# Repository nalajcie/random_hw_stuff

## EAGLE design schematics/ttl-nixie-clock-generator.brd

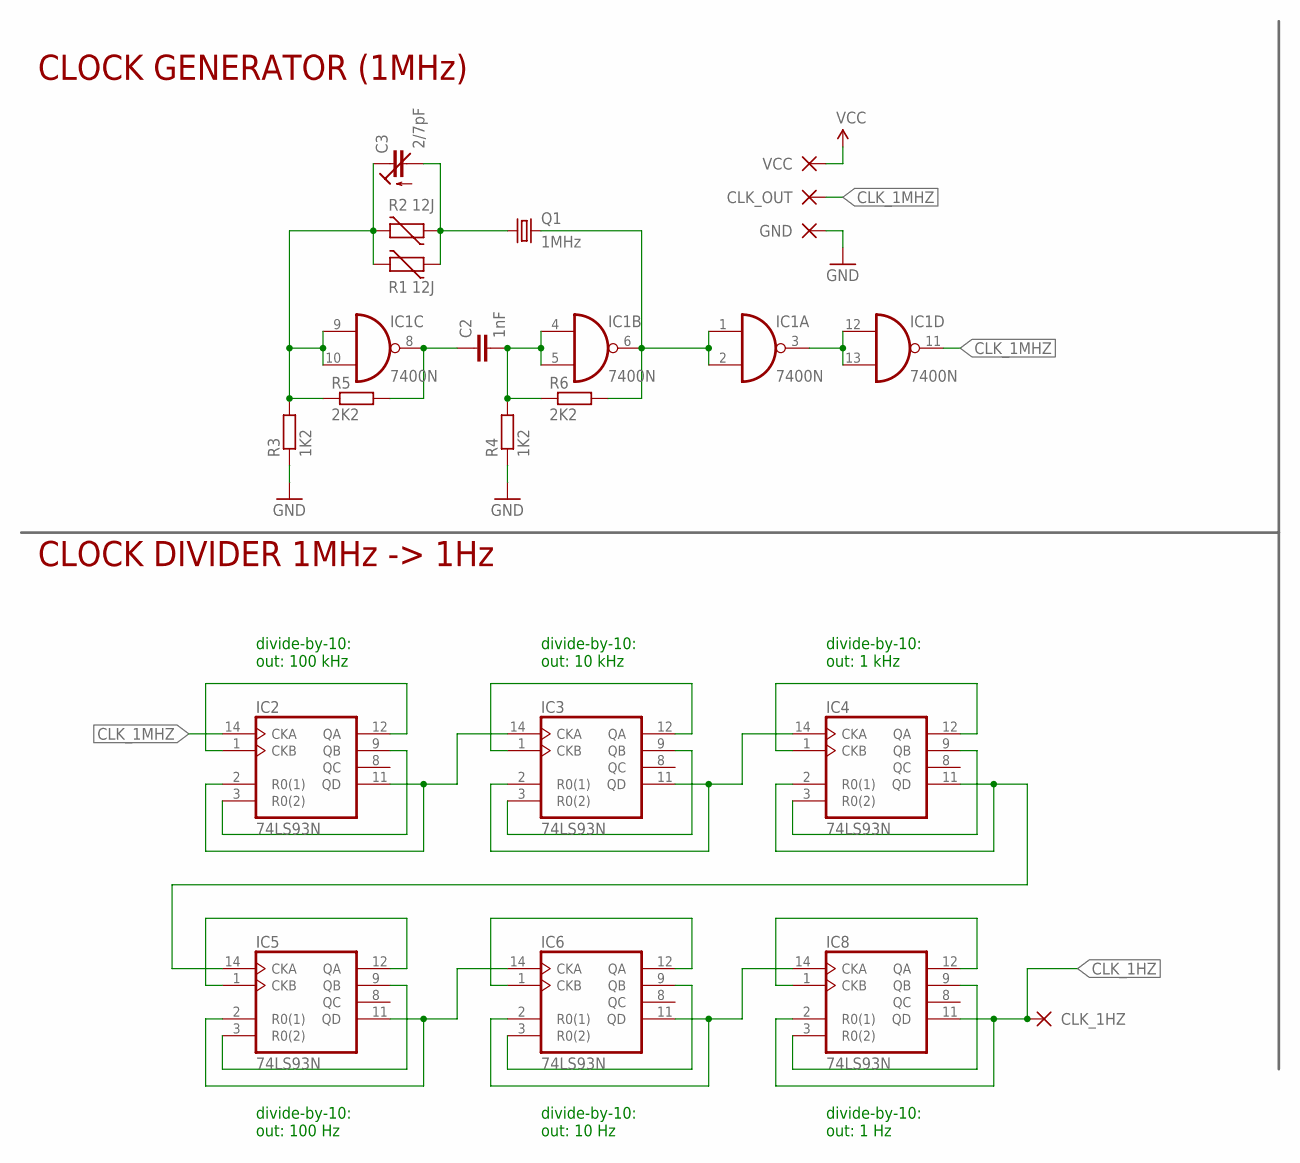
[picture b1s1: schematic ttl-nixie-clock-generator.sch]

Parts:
C2: 1nF; C15B5
C3: 2/7pF; CTRIM808-BC7.5
CLK_1HZ: VCC; 2,15/1,0
CLK_OUT: CLK_OUT; 2,15/1,0
GND: GND; 2,15/1,0
IC1: 7400N; DIL14
IC2, IC3, IC4, IC5, IC6, IC8: 74LS93N; DIL14
Q1: 1MHz; HC33U-V
R1, R2: 12J; R-7,5
R3, R4: 1K2; 0207/12
R5, R6: 2K2; 0207/12
VCC: VCC; 2,15/1,0

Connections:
CLK_1HZ: CLK_1HZ.1, IC8.2 (R0(1)), IC8.11 (QD)
CLK_1MHZ: CLK_OUT.1, IC1.11 (O), IC2.14 (CKA)
GND: GND.1, IC1.7 (GND), IC2.10 (GND), IC3.10 (GND), IC4.10 (GND), IC5.10 (GND), IC6.10 (GND), IC8.10 (GND), R3.1, R4.1
unnamed: C3.2 (A), Q1.1, R1.1, R2.1
unnamed: C3.1 (E), IC1.9 (I0), IC1.10 (I1), R1.2, R2.2, R3.2, R5.1
unnamed: IC1.3 (O), IC1.12 (I0), IC1.13 (I1)
unnamed: C2.1, IC1.8 (O), R5.2
unnamed: C2.2, IC1.4 (I0), IC1.5 (I1), R4.2, R6.1
unnamed: IC1.1 (I0), IC1.2 (I1), IC1.6 (O), Q1.2, R6.2
unnamed: IC5.1 (CKB), IC5.12 (QA)
unnamed: IC5.3 (R0(2)), IC5.9 (QB)
unnamed: IC5.2 (R0(1)), IC5.11 (QD), IC6.14 (CKA)
unnamed: IC6.1 (CKB), IC6.12 (QA)
unnamed: IC6.3 (R0(2)), IC6.9 (QB)
unnamed: IC6.2 (R0(1)), IC6.11 (QD), IC8.14 (CKA)
unnamed: IC8.1 (CKB), IC8.12 (QA)
unnamed: IC8.3 (R0(2)), IC8.9 (QB)
unnamed: IC2.1 (CKB), IC2.12 (QA)
unnamed: IC2.2 (R0(1)), IC2.11 (QD), IC3.14 (CKA)
unnamed: IC2.3 (R0(2)), IC2.9 (QB)
unnamed: IC3.3 (R0(2)), IC3.9 (QB)
unnamed: IC3.2 (R0(1)), IC3.11 (QD), IC4.14 (CKA)
unnamed: IC3.1 (CKB), IC3.12 (QA)
unnamed: IC4.1 (CKB), IC4.12 (QA)
unnamed: IC4.3 (R0(2)), IC4.9 (QB)
unnamed: IC4.2 (R0(1)), IC4.11 (QD), IC5.14 (CKA)
VCC: IC1.14 (VCC), IC2.5 (VCC), IC3.5 (VCC), IC4.5 (VCC), IC5.5 (VCC), IC6.5 (VCC), IC8.5 (VCC), VCC.1

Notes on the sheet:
divide-by-10: out: 100 kHz
divide-by-10: out: 10 kHz
divide-by-10: out: 1 kHz
divide-by-10: out: 100 Hz
divide-by-10: out: 10 Hz
divide-by-10: out: 1 Hz
CLOCK DIVIDER 1MHz -> 1Hz
CLOCK GENERATOR (1MHz)

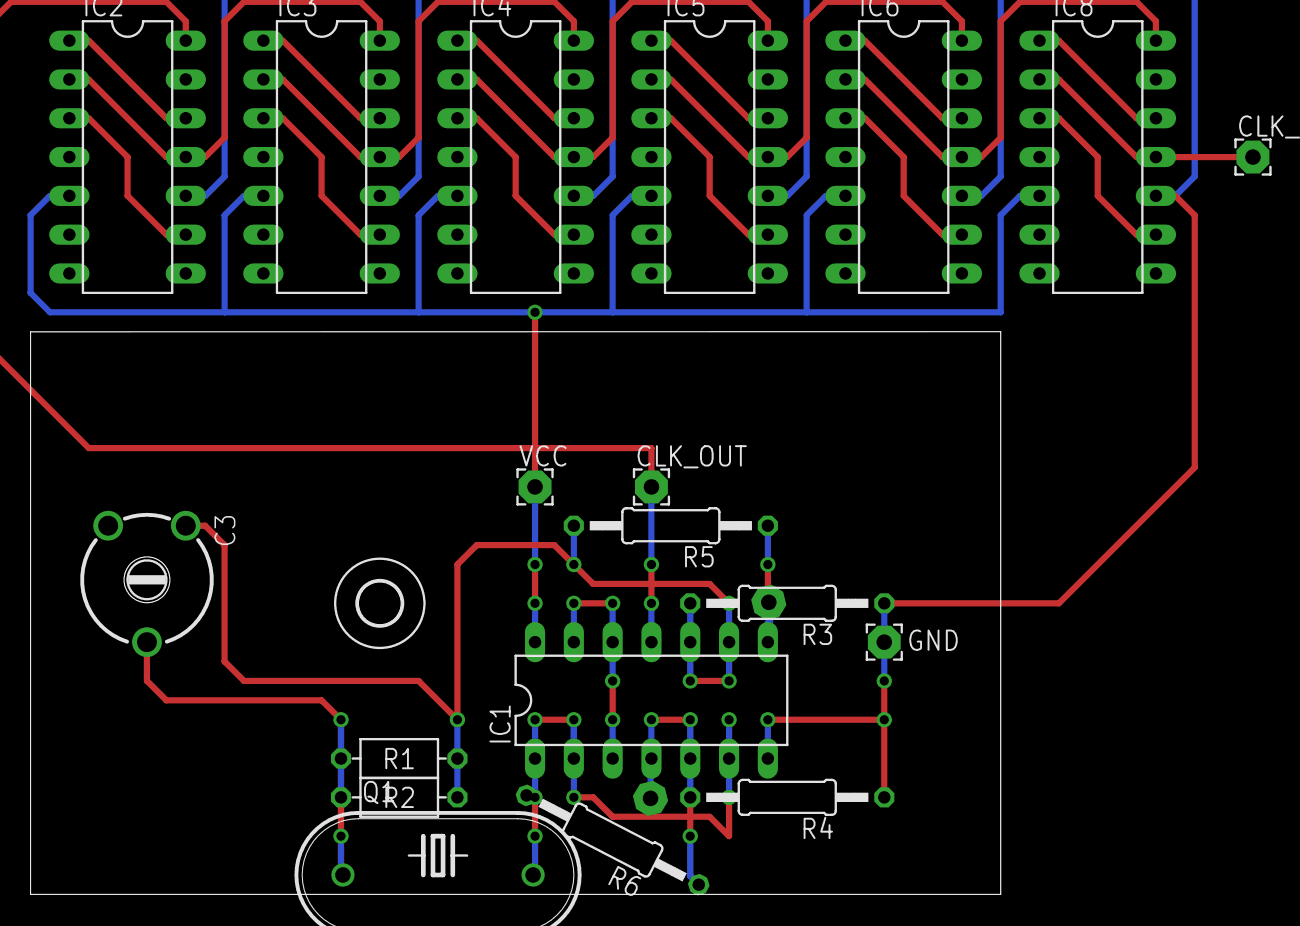
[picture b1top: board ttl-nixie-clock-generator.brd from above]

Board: 2 copper layers, 63.5 x 36.8 mm, 21 parts (1 on the bottom side), 27 nets.

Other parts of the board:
U$1: 2,8

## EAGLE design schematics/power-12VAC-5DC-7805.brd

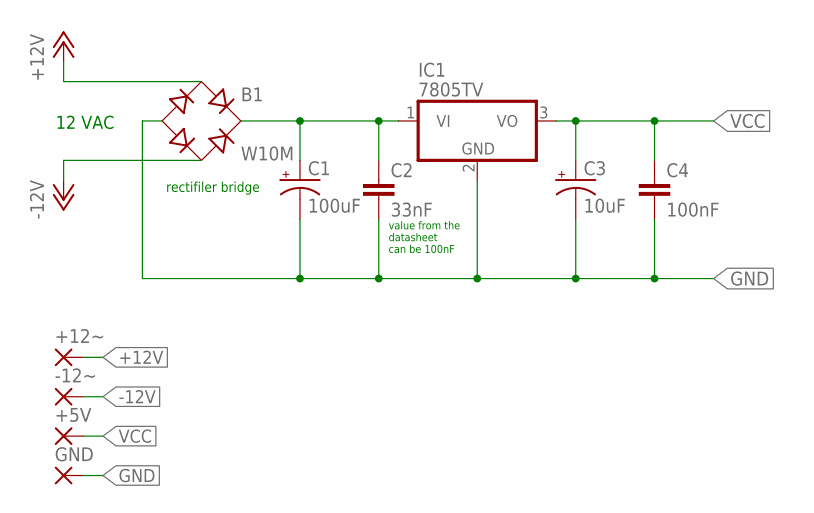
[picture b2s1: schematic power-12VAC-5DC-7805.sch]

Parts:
+5V, +12~: WIREPAD2,15/1,0; 2,15/1,0
-12~: WIREPAD2,15/1,0; 2,15/1,0
B1: W10M; RB1A
C1: 100uF; CPOL-RADIAL-100UF-25V
C2: 33nF; CAP-PTH-SMALL
C3: 10uF; CPOL-RADIAL-100UF-25V
C4: 100nF; CAP-PTH-SMALL
GND: WIREPAD2,15/1,0; 2,15/1,0
IC1: 7805TV; TO220V

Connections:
+12V: +12~.1, B1.AC1
-12V: -12~.1, B1.AC2
GND: B1.-, C1.2 (-), C2.2, C3.2 (-), C4.2, GND.1, IC1.2 (GND)
unnamed: B1.+, C1.1 (+), C2.1, IC1.1 (VI)
VCC: +5V.1, C3.1 (+), C4.1, IC1.3 (VO)

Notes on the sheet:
value from the datasheet can be 100nF
12 VAC
rectifiler bridge

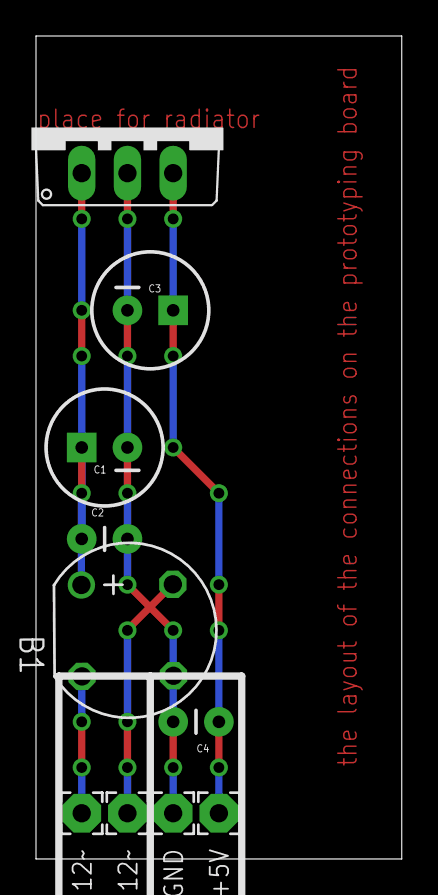
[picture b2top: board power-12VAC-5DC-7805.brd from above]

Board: 2 copper layers, 20.3 x 45.7 mm, 10 parts (0 on the bottom side), 5 nets.

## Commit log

2015-08-18 :octocat: Added .gitattributes & .gitignore files
2015-08-18 gitignore: add eagle backup files
2015-08-18 schematics: schema of NAND TTL quartz generator found in old nixie clock
2015-08-18 schematics: add png
2015-08-18 schematics: add power supply 12VAC/5DC based on 7805
2015-08-19 schematics: add wiredpads
2015-08-19 schematics: wiring power supply on protoboard
2015-08-21 schenatics: ttl-generator: protoboard version
2015-08-22 ttl-generator: protoboard built version
    The version i built on protoboard, it works!
    The multimeter says 999.7 kHz :)
2015-08-23 power-supply: better components placement on stripboard
2015-08-26 power supply: new stripboard layout
2015-08-26 nixie-clock-generator: added divide circuit, prettify
2015-09-13 schematics: nixie clock control based on 7400
2015-09-13 schematics: pdf update

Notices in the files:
parts and their libraries:
SparkFun-Capacitors: Licensing: Creative Commons ShareAlike 4.0 International - https://creativecommons.org/licenses/by-sa/4.0
